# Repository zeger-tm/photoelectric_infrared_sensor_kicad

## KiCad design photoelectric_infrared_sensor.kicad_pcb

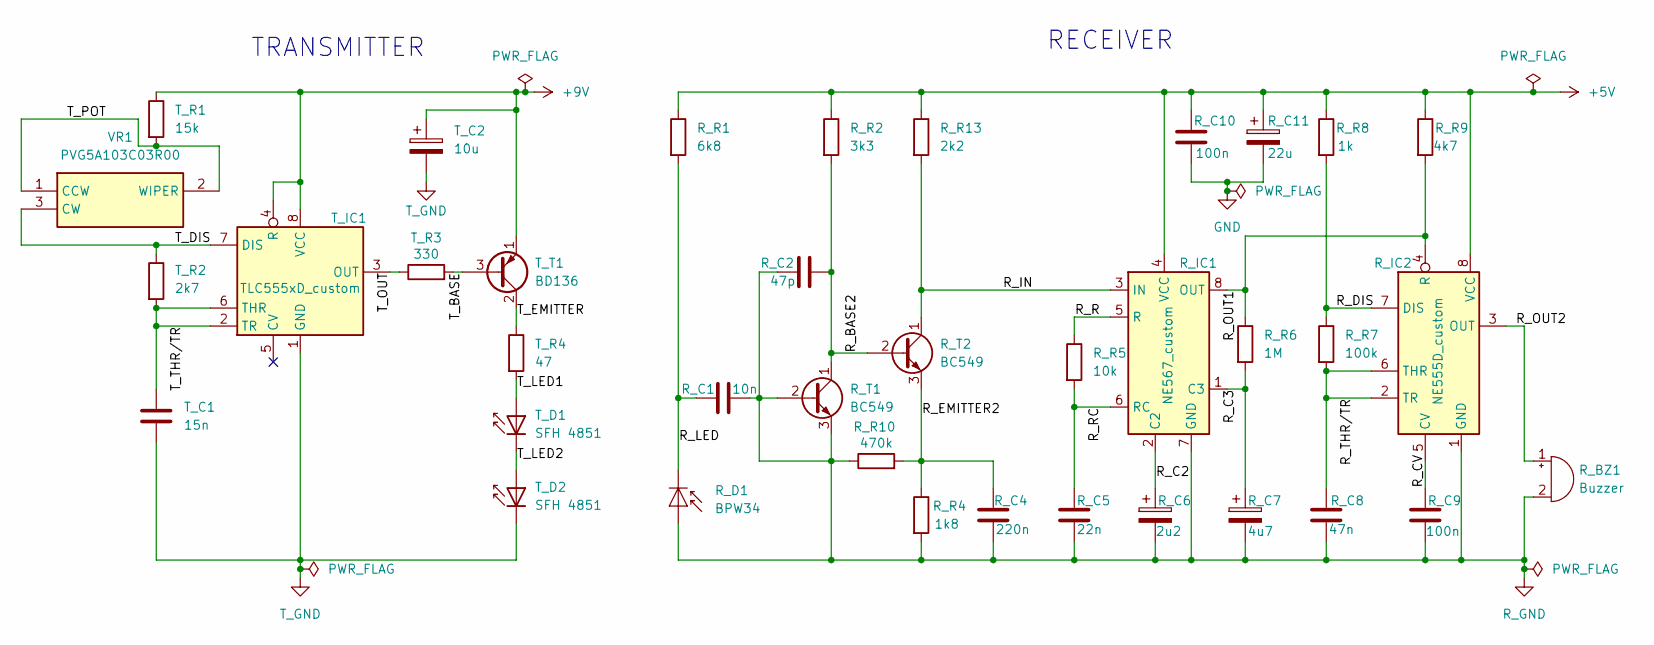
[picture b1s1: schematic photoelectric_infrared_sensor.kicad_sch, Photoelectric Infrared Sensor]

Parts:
R_BZ1: Buzzer; CPT-1203-03-SMT-TR
R_C1: 10n; C_0402_1005Metric_Pad0.74x0.62mm_HandSolder
R_C2: 47p; C_0402_1005Metric_Pad0.74x0.62mm_HandSolder
R_C4: 220n; C_0402_1005Metric_Pad0.74x0.62mm_HandSolder
R_C5: 22n; C_0402_1005Metric_Pad0.74x0.62mm_HandSolder
R_C6: 2u2; CP_Elec_4x3
R_C7: 4u7; CP_Elec_4x3
R_C8: 47n; C_0402_1005Metric_Pad0.74x0.62mm_HandSolder
R_C9, R_C10: 100n; C_0402_1005Metric_Pad0.74x0.62mm_HandSolder
R_C11: 22u; CP_Elec_4x3
R_D1: BPW34; BPW34FASZ
R_IC1: NE567_custom; SOIC-8_3.9x4.9mm_P1.27mm
R_IC2: NE555D_custom; SOIC-8_3.9x4.9mm_P1.27mm
R_R1: 6k8; ERJUP6
R_R2: 3k3; ERJUP6
R_R4: 1k8; ERJUP6
R_R5: 10k; ERJUP6
R_R6: 1M; ERJUP6
R_R7: 100k; ERJUP6
R_R8: 1k; ERJUP6
R_R9: 4k7; ERJUP6
R_R10: 470k; ERJUP6
R_R13: 2k2; ERJUP6
R_T1, R_T2: BC549; TO-92_Inline
T_C1: 15n; C_0402_1005Metric_Pad0.74x0.62mm_HandSolder
T_C2: 10u; CP_Elec_3x5.4
T_D1, T_D2: SFH 4851; SFH4851
T_IC1: TLC555xD_custom; SOIC-8_3.9x4.9mm_P1.27mm
T_R1: 15k; ERJUP6
T_R2: 2k7; ERJUP6
T_R3: 330; ERJUP6
T_R4: 47; ERJS1T_U1T__2512_
T_T1: BD136; TO-126-3_Vertical
VR1: PVG5A103C03R00; PVG5A100C03R00; Manufacturer_Part_Number PVG5A103C03R00; Mouser Part Number 81-PVG5A103C03R00

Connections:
+5V: R_C10.1, R_C11.1, R_IC1.4 (VCC), R_IC2.8 (VCC), R_R1.1, R_R2.1, R_R8.1, R_R9.1, R_R13.1
+9V: T_C2.1, T_IC1.4 (R), T_IC1.8 (VCC), T_R1.1, T_T1.1 (E)
/R_BASE2: R_C2.2, R_R2.2, R_T1.1 (C), R_T2.2 (B)
/R_C2: R_C6.1, R_IC1.2 (C2)
/R_C3: R_C7.1, R_IC1.1 (C3), R_R6.2
/R_CV: R_C9.1, R_IC2.5 (CV)
/R_DIS: R_IC2.7 (DIS), R_R7.1, R_R8.2
/R_EMITTER2: R_C4.1, R_R4.1, R_R10.2, R_T2.3 (E)
/R_IN: R_IC1.3 (IN), R_R13.2, R_T2.1 (C)
/R_LED: R_C1.2, R_D1.1 (K), R_R1.2
/R_OUT1: R_IC1.8 (OUT), R_IC2.4 (R), R_R6.1, R_R9.2
/R_OUT2: R_BZ1.1 (+), R_IC2.3 (OUT)
/R_R: R_IC1.5 (R), R_R5.1
/R_RC: R_C5.1, R_IC1.6 (RC), R_R5.2
/R_THR/TR: R_C8.1, R_IC2.2 (TR), R_IC2.6 (THR), R_R7.2
/T_BASE: T_R3.2, T_T1.3 (B)
/T_DIS: T_IC1.7 (DIS), T_R2.1, VR1.3 (CW); also elsewhere on the board
/T_EMITTER: T_R4.1, T_T1.2 (C)
/T_LED1: T_D1.2 (A), T_R4.2
/T_LED2: T_D1.1 (K), T_D2.2 (A)
/T_OUT: T_IC1.3 (OUT), T_R3.1
/T_POT: T_R1.2, VR1.1 (CCW), VR1.2 (WIPER); also elsewhere on the board
/T_THR/TR: T_C1.1, T_IC1.2 (TR), T_IC1.6 (THR), T_R2.2
GND: R_C10.2, R_C11.2
R_GND: R_BZ1.2 (-), R_C1.1, R_C2.1, R_C4.2, R_C5.2, R_C6.2, R_C7.2, R_C8.2, R_C9.2, R_D1.2 (A), R_IC1.7 (GND), R_IC2.1 (GND), R_R4.2, R_R10.1, R_T1.2 (B), R_T1.3 (E)
T_GND: T_C1.2, T_C2.2, T_D2.1 (K), T_IC1.1 (GND)

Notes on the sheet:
RECEIVER
TRANSMITTER

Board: 4 copper layers, 37 parts (0 on the bottom side), 26 nets, no tracks yet.

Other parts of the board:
T_P1: PVG5A103C03R00; PVG5A100C03R00

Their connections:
/T_DIS: T_P1.3 (CW); also elsewhere on the board
/T_POT: T_P1.1 (CCW), T_P1.2 (WIPER); also elsewhere on the board

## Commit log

2024-12-08 added BOM
2024-12-09 finished schematics
2024-12-10 added schematics as .pdf
2024-12-14 enter the commit message for your changes. Lines starting
